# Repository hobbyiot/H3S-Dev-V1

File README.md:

# H3S-Dev board for building Meshtastic nodes

### The new H3S-Dev design is alive!

#
## This project was sponsored by [PCBWay](https://www.pcbway.com/)
### They offer a turnkey service to manufacture and assemble your printed circuit boards! The whole operation is fast and reliable since every single step is agreed between the customer and the responsible people from the factory. Every one detail is discussed as the components and materials used are agreed on at a high professional level.

## Arrival and first impressions

All prototypes came as usual from that manufacturer - individually and safely packed within the parcel - directly from the factory!

H3S-Dev board     |  Unpacking
:-------------------------:|:-------------------------:
 | 

### 

#

### Specifications:
-  MCU:  ESP32-S3 with 8MB PSRAM
-  LoRa: RA-01SH-P with Power amplifier
-  GNSS: L96-M33 or similar
-  Power: USB-C and additional input (for example solar source) with separate sensing
-  LiPo battery management
-  I2C extension slots and soldering area
-  Credit card size 2-layer PCB
-  KiCad design open source hardware
#

### As a successor of our recent [H2S-Dev board](https://github.com/hobbyiot/LoRa-Nodes) the new hardware is compatible with both Meshtastic and Helium networks, ready to setup a simple node, sensor or tracker of your choice!

#

#
### Circuit schematic:

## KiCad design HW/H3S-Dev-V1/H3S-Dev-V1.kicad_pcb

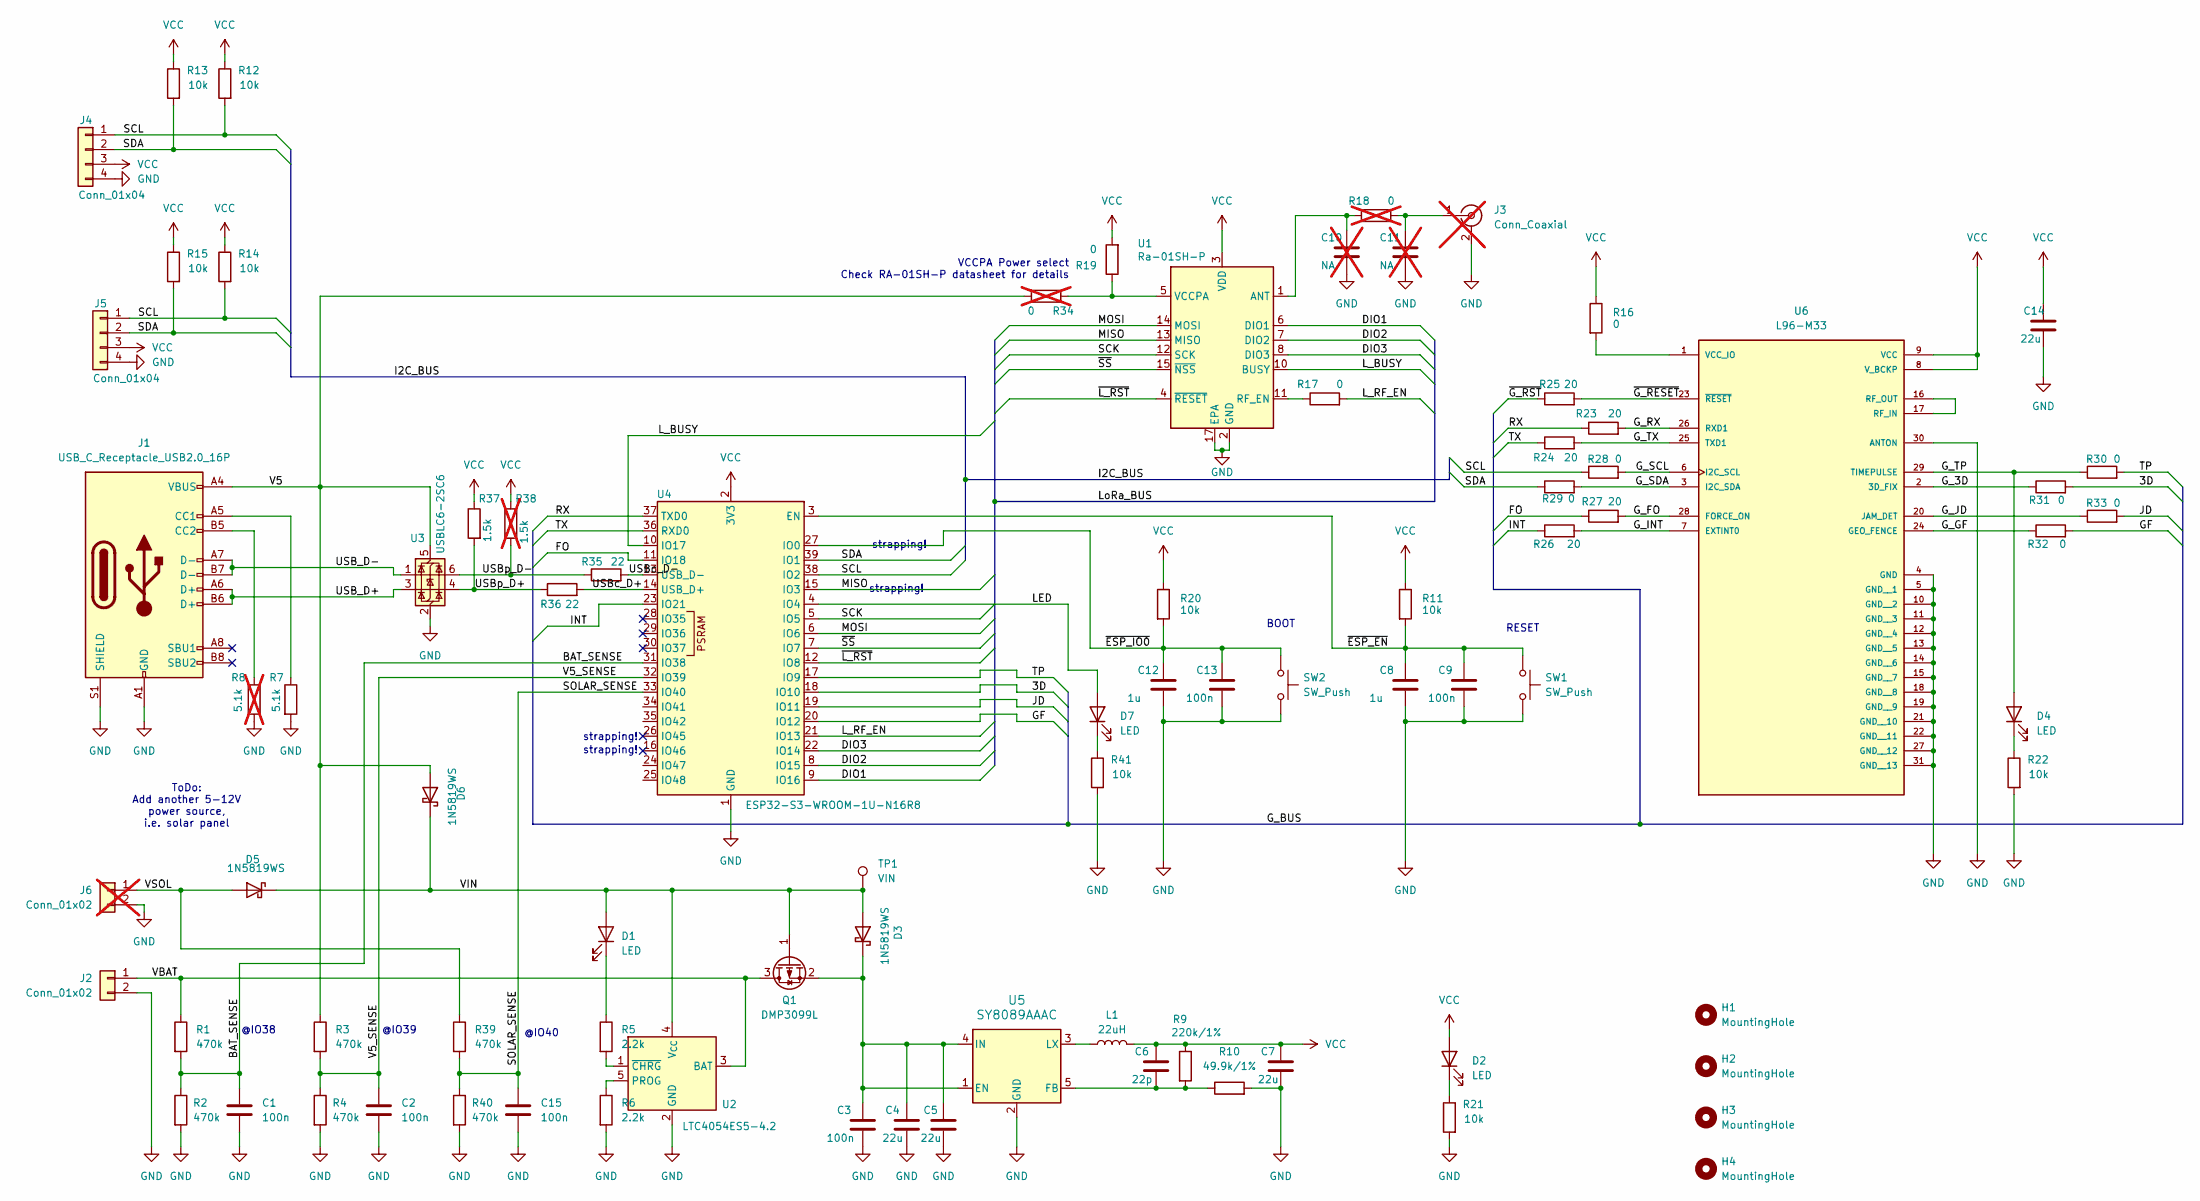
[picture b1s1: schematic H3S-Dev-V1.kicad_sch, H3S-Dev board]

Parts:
C1, C2, C3, C9, C13, C15: 100n; C_0603_1608Metric
C4, C5: 22u; C_0805_2012Metric
C6: 22p; C_0603_1608Metric
C7, C14: 22u; C_0805_2012Metric_Pad1.18x1.45mm_HandSolder
C8, C12: 1u; C_0603_1608Metric
C10, C11: NA; C_0402_1005Metric; not fitted
D1, D2, D4, D7: LED; LED_0603_1608Metric
D3, D5, D6: 1N5819WS; D_SOD-323
H1, H2, H3, H4: MountingHole; MountingHole_2.2mm_M2
J1: USB_C_Receptacle_USB2.0_16P; USB_C_Receptacle_GCT_USB4105-xx-A_16P_TopMnt_Horizontal
J2: Conn_01x02; JST_PH_B2B-PH-K_1x02_P2.00mm_Vertical
J3: Conn_Coaxial; U.FL_Hirose_U.FL-R-SMT-1_Vertical; not fitted
J4, J5: Conn_01x04; NS-Tech_Grove_1x04_P2mm_Vertical
J6: Conn_01x02; JST_XA_B02B-XASK-1_1x02_P2.50mm_Vertical; not fitted
L1: 22uH; L_Wurth_WE-LQSH-4020
Q1: DMP3099L; SOT-23
R1, R2, R3, R4, R39, R40: 470k; R_0603_1608Metric
R5, R6: 2.2k; R_0603_1608Metric
R7: 5.1k; R_0603_1608Metric
R8: 5.1k; R_0603_1608Metric; not fitted
R9: 220k/1%; R_0603_1608Metric
R10: 49.9k/1%; R_0603_1608Metric
R11, R12, R13, R14, R15, R20, R21, R22, R41: 10k; R_0603_1608Metric
R16, R17, R19, R28, R29, R30, R31, R32, R33: 0; R_0603_1608Metric
R18: 0; R_0402_1005Metric; not fitted
R23, R24, R25, R26, R27: 20; R_0603_1608Metric
R34: 0; R_0603_1608Metric; not fitted
R35, R36: 22; R_0603_1608Metric
R37: 1.5k; R_0603_1608Metric
R38: 1.5k; R_0603_1608Metric; not fitted
SW1, SW2: SW_Push; SW_Tactile_SPST_NO_Straight_CK_PTS636Sx25SMTRLFS
TP1: VIN; PinHeader_1x01_P1.27mm_Vertical
U1: Ra-01SH-P
U2: LTC4054ES5-4.2; TSOT-23-5
U3: USBLC6-2SC6; SOT-23-6
U4: ESP32-S3-WROOM-1U-N16R8; ESP32-S3-WROOM-1U
U5: SY8089AAAC; SOT-23-5
U6: L96-M33; XCVR_L96-M33

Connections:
/3D: R31.2, U4.18 (IO10)
/BAT_SENSE: C1.1, R1.2, R2.1, U4.31 (IO38)
/DIO1: U1.6 (DIO1), U4.9 (IO16)
/DIO2: U1.7 (DIO2), U4.8 (IO15)
/DIO3: U1.8 (DIO3), U4.22 (IO14)
/FO: R27.1, U4.11 (IO18)
/GF: R32.2, U4.20 (IO12)
/G_3D: R31.1, U6.2 (3D_FIX)
/G_FO: R27.2, U6.28 (FORCE_ON)
/G_GF: R32.1, U6.24 (GEO_FENCE)
/G_INT: R26.2, U6.7 (EXTINT0)
/G_JD: R33.1, U6.20 (JAM_DET)
/G_RX: R23.2, U6.26 (RXD1)
/G_SCL: R28.2, U6.6 (I2C_SCL)
/G_SDA: R29.2, U6.3 (I2C_SDA)
/G_TP: D4.2 (A), R30.1, U6.29 (TIMEPULSE)
/G_TX: R24.2, U6.25 (TXD1)
/INT: R26.1, U4.23 (IO21)
/JD: R33.2, U4.19 (IO11)
/LED: D7.2 (A), U4.4 (IO4)
/L_BUSY: U1.10 (BUSY), U4.10 (IO17)
/L_RF_EN: R17.2, U4.21 (IO13)
/MISO: U1.13 (MISO), U4.15 (IO3)
/MOSI: U1.14 (MOSI), U4.6 (IO6)
/RX: R23.1, U4.37 (TXD0)
/SCK: U1.12 (SCK), U4.5 (IO5)
/SCL: J4.1, J5.1, R12.2, R14.2, R28.1, U4.38 (IO2)
/SDA: J4.2, J5.2, R13.2, R15.2, R29.1, U4.39 (IO1)
/SOLAR_SENSE: C15.1, R39.2, R40.1, U4.33 (IO40)
/TP: R30.2, U4.17 (IO9)
/TX: R24.1, U4.36 (RXD0)
/USB_D+: J1.A6 (D+), J1.B6 (D+), U3.3 (I/O2)
/USB_D-: J1.A7 (D-), J1.B7 (D-), U3.1 (I/O1)
/USBc_D+: R36.2, U4.14 (USB_D+)
/USBc_D-: R35.2, U4.13 (USB_D-)
/USBp_D+: R36.1, R37.2, U3.4 (I/O2)
/USBp_D-: R35.1, R38.2, U3.6 (I/O1)
/V5: D6.2 (A), J1.A4 (VBUS), J1.A9 (VBUS), J1.B4 (VBUS), J1.B9 (VBUS), R3.1, R34.2, U3.5 (VBUS)
/V5_SENSE: C2.1, R3.2, R4.1, U4.32 (IO39)
/VBAT: J2.1, Q1.3 (D), R1.1, U2.3 (BAT)
/VIN: D1.2 (A), D3.2 (A), D5.1 (K), D6.1 (K), Q1.1 (G), TP1.1, U2.4 (V_{CC})
/VSOL: D5.2 (A), J6.1, R39.1
/~ESP_EN: C8.1, C9.1, R11.2, SW1.1, U4.3 (EN)
/~ESP_IO0: C12.1, C13.1, R20.2, SW2.1, U4.27 (IO0)
/~G_RESET: R25.2, U6.23 (~RESET)
/~G_RST: R25.1
/~L_RST: U1.4 (~RESET), U4.12 (IO8)
/~SS: U1.15 (~NSS), U4.7 (IO7)
GND: C1.2, C2.2, C3.2, C4.2, C5.2, C7.2, C8.2, C9.2, C10.2, C11.2, C12.2, C13.2, C14.2, C15.2, J1.A1 (GND), J1.A12 (GND), J1.B1 (GND), J1.B12 (GND), J1.S1 (SHIELD), J2.2, J3.2 (Ext), J4.4, J5.4, J6.2, R2.2, R4.2, R6.2, R7.2, R8.2, R10.2, R21.2, R22.2, R40.2, R41.2, SW1.2, SW2.2, U1.2 (GND), U1.9 (GND), U1.16 (GND), U1.17 (EPA), U2.2 (GND), U3.2 (GND), U4.1 (GND), U4.40 (GND), U4.41 (GND), U5.2 (GND), U6.4 (GND), U6.5 (GND__1), U6.10 (GND__2), U6.11 (GND__3), U6.12 (GND__4), U6.13 (GND__5), U6.14 (GND__6), U6.15 (GND__7), U6.18 (GND__8), U6.19 (GND__9), U6.21 (GND__10), U6.22 (GND__11), U6.27 (GND__12), U6.30 (ANTON), U6.31 (GND__13)
unnamed: D1.1 (K), R5.1
unnamed: D2.1 (K), R21.1
unnamed: C3.1, C4.1, C5.1, D3.1 (K), Q1.2 (S), U5.1 (EN), U5.4 (IN)
unnamed: D4.1 (K), R22.1
unnamed: D7.1 (K), R41.1
unnamed: J1.A5 (CC1), R7.1
unnamed: J1.B5 (CC2), R8.1
unnamed: C11.1, J3.1 (In), R18.2
unnamed: C10.1, R18.1, U1.1 (ANT)
unnamed: R17.1, U1.11 (RF_EN)
unnamed: R19.1, R34.1, U1.5 (VCCPA)
unnamed: R6.1, U2.5 (PROG)
unnamed: R5.2, U2.1 (~CHRG)
unnamed: C6.2, R9.2, R10.1, U5.5 (FB)
unnamed: L1.2, U5.3 (LX)
unnamed: U6.16 (RF_OUT), U6.17 (RF_IN)
unnamed: R16.2, U6.1 (VCC_IO)
VCC: C6.1, C7.1, C14.1, D2.2 (A), J4.3, J5.3, L1.1, R9.1, R11.1, R12.1, R13.1, R14.1, R15.1, R16.1, R19.2, R20.1, R37.1, R38.1, U1.3 (VDD), U4.2 (3V3), U6.8 (V_BCKP), U6.9 (VCC)

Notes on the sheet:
@IO38
strapping!
BOOT
ToDo: Add another 5-12V power source, i.e. solar panel
RESET
@IO39
VCCPA Power select Check RA-01SH-P datasheet for details
@IO40

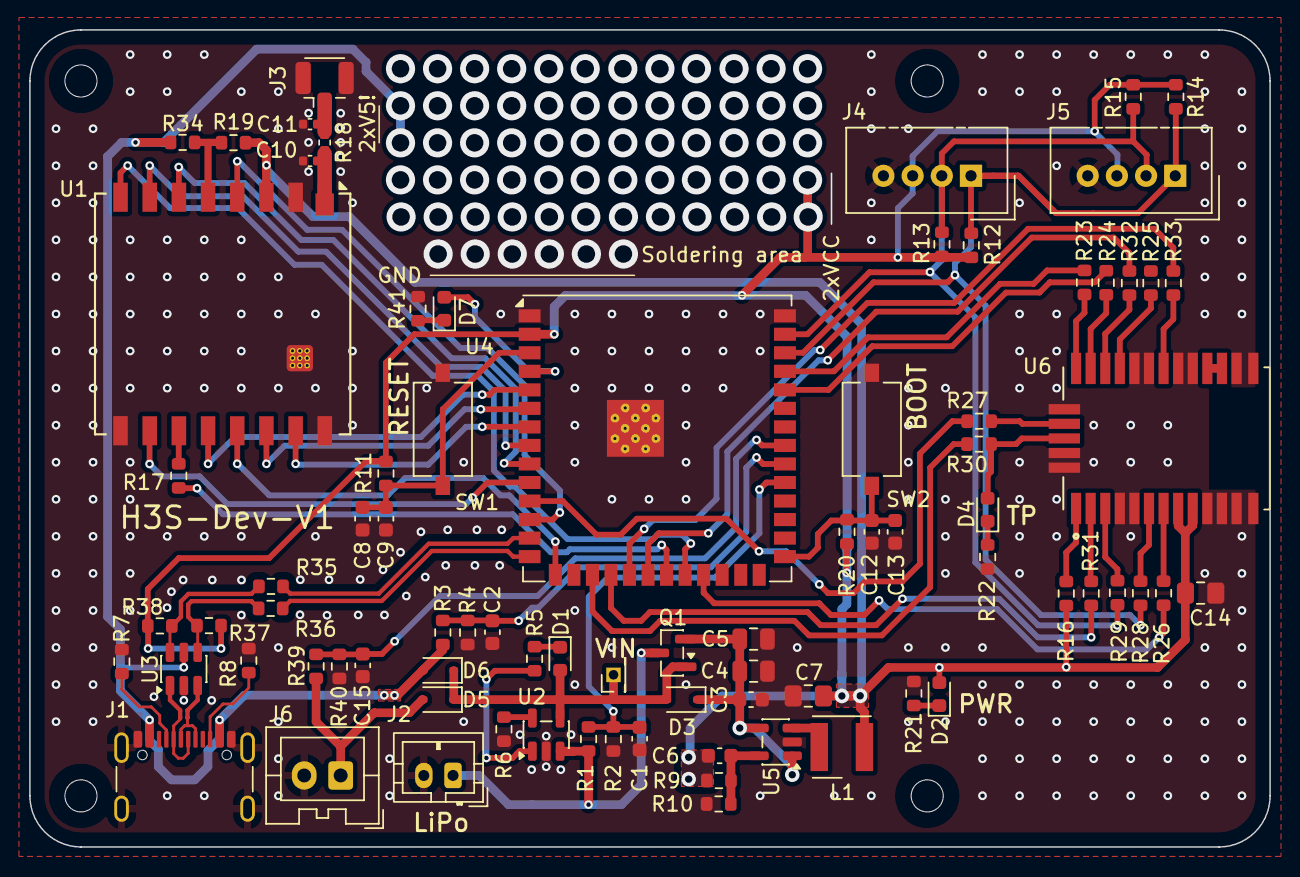
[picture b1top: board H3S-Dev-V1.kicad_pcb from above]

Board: 2 copper layers, 85.0 x 56.0 mm, 84 parts (0 on the bottom side), 66 nets.

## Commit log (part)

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2026-02-17 USB Updated
2026-02-17 Create LICENSE
2026-02-18 Some components arranged
2026-02-21 Charger works
2026-02-22 PCB dimensions
2026-02-23 dc-dc routing
2026-02-27 LoRa, Reset and some more routing
2026-03-01 Some progress ...
2026-03-01 GNSS Module added
2026-03-01 GNSS Module models
2026-03-05 Some progress...
2026-03-12 RA-01SH-P LoRa module added
2026-03-13 J2 updated
2026-03-13 New picture WiP 3
2026-03-13 LoRa updates
2026-03-13 Footprint updated
2026-03-13 Update README.md
    Picture updated
2026-03-15 Minor changes
2026-03-27 Some progress
2026-05-24 LoRa intereface connected
